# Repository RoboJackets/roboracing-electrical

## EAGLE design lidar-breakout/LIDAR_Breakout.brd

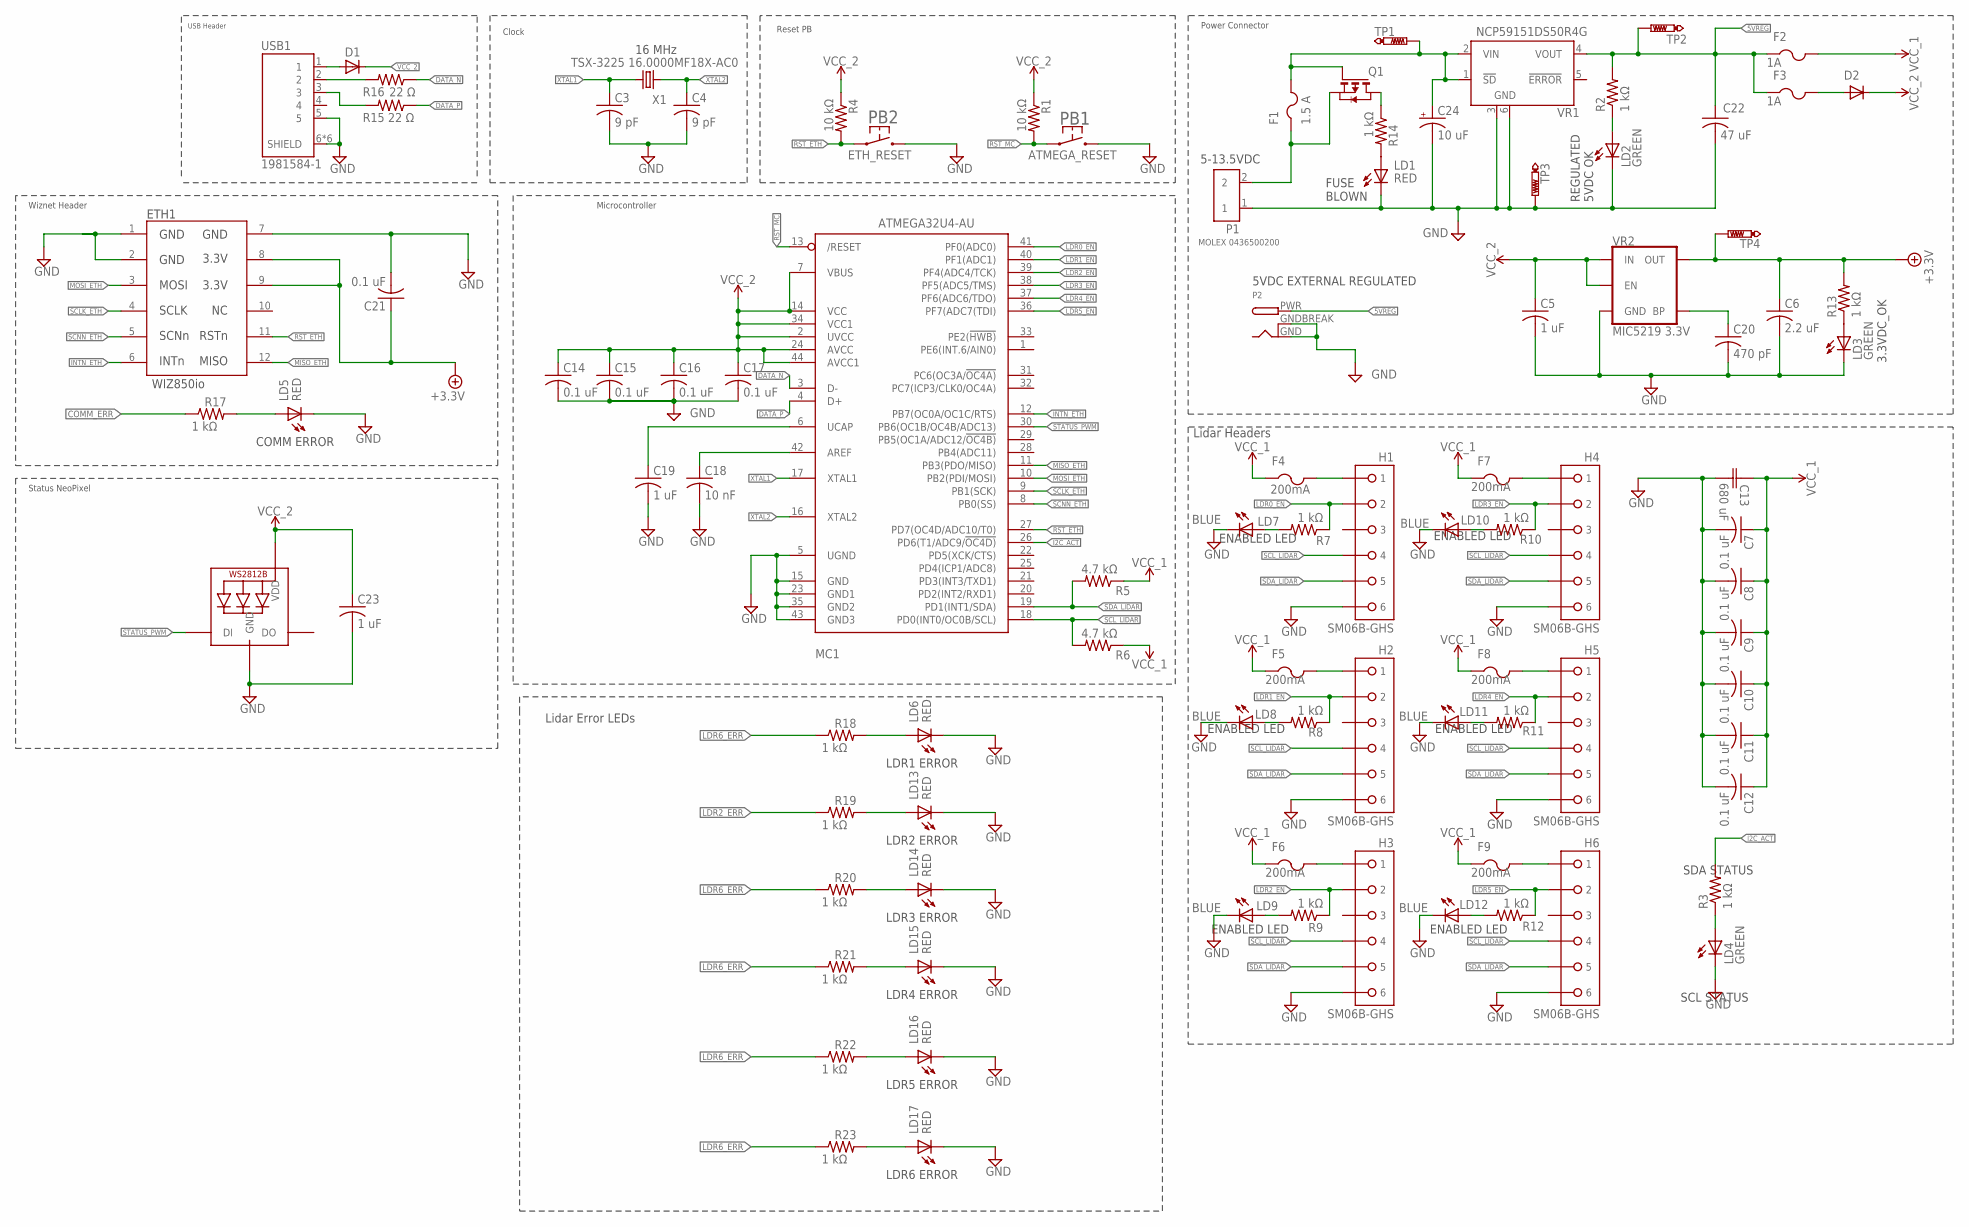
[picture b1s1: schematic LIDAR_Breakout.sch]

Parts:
C3, C4: 9 pF; C0603
C5, C19, C23: 1 uF; C0603
C6: 2.2 uF; C0603
C7, C8, C9, C10, C11, C12, C14, C15, C16, C17, C21: 0.1 uF; C0603
C13: 680 uF; CAP_PAN_EEE_D8
C18: 10 nF; C0603
C20: 470 pF; C0603
C22: 47 uF; C0805
C24: 10 uF; E2-5
D1, D2: DIODE-DO-214AC; DO-214AC
ETH1: WIZ850IO
F1: 1.5 A; 1812
F2, F3: 1A; R1206
F4, F5, F6, F7, F8, F9: 200mA; R1206
H1, H2, H3, H4, H5, H6: SM06B-GHS
LD1, LD5, LD6, LD13, LD14, LD15, LD16, LD17: RED; CHIP-LED0603
LD2, LD3, LD4: GREEN; CHIP-LED0603
LD7, LD8, LD9, LD10, LD11, LD12: BLUE; CHIP-LED0603
LED1: WS2812B5050; WS2812B
MC1: ATMEGA32U4-AU; TQFP44
P1: MOLEX 0436500200; MOLEX_0436500200
P2: DCBARRELPTH; DCJACK_2MM_PTH
PB1: ATMEGA_RESET; RESET_PB_RA
PB2: ETH_RESET; RESET_PB_RA
Q1: PMOS; SOT-23-3
R1, R4: 10 kΩ; R0603
R2, R3, R7, R8, R9, R10, R11, R12, R13, R14, R17, R18, R19, R20, R21, R22, R23: 1 kΩ; R0603
R5, R6: 4.7 kΩ; R0603
R15, R16: 22 Ω; R0603
TP1, TP2, TP4: PTR1B1,27; B1,27
TP3: PTR1PAD1-13; P1-13
USB1: 1981584-1; TE_1981584-1
VR1: NCP59151DS50R4G; TO263-5
VR2: MIC5219 3.3V; SOT23-5
X1: TSX-3225 16.0000MF18X-AC0; XTAL-3.2X2.5

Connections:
5VREG: C22.1, F2.1, F3.1, P2.PWR, R2.2, TP2.TP, VR1.4 (VOUT)
+3.3V: C6.1, C21.1, ETH1.8, ETH1.9, R13.2, TP4.TP, VR2.5 (OUT)
AREF: C18.1, MC1.42 (AREF)
COMM_ERR: R17.1
DATA_N: MC1.3 (D-), R16.1
DATA_P: MC1.4 (D+), R15.1
GND: C3.2, C4.2, C5.2, C6.2, C7.2, C8.2, C9.2, C10.2, C11.2, C12.2, C13.2 (22), C14.2, C15.2, C16.2, C17.2, C18.2, C19.2, C20.2, C21.2, C22.2, C23.2, C24.-, ETH1.1, ETH1.2, ETH1.7, H1.P$8 (6), H2.P$8 (6), H3.P$8 (6), H4.P$8 (6), H5.P$8 (6), H6.P$8 (6), LD1.C (K), LD2.C, LD3.C, LD4.C, LD5.C (K), LD6.C (K), LD7.C, LD8.C, LD9.C, LD10.C, LD11.C, LD12.C, LD13.C (K), LD14.C (K), LD15.C (K), LD16.C (K), LD17.C (K), LED1.3-GND (GND), MC1.5 (UGND), MC1.15 (GND), MC1.23 (GND1), MC1.35 (GND2), MC1.43 (GND3), P1.1, P2.GND, P2.GNDBREAK, PB1.P$3 (2), PB2.P$3 (2), TP3.TP, USB1.5, USB1.6 (SHIELD), USB1.7 (SHIELD), USB1.8 (SHIELD), USB1.9 (SHIELD), USB1.10 (SHIELD), USB1.11 (SHIELD), VR1.3 (GND), VR1.6 (GND), VR2.2 (GND)
I2C_ACT: MC1.26 (PD6(T1/ADC9/!OC4D)), R3.2
INTN_ETH: ETH1.6, MC1.12 (PB7(OC0A/OC1C/RTS))
LDR0_EN: H1.P$4 (2), MC1.41 (PF0(ADC0)), R7.1
LDR0_LED: LD7.A, R7.2
LDR1_EN: H2.P$4 (2), MC1.40 (PF1(ADC1)), R8.1
LDR1_LED: LD8.A, R8.2
LDR2_EN: H3.P$4 (2), MC1.39 (PF4(ADC4/TCK)), R9.1
LDR2_ERR: R19.1
LDR2_LED: LD9.A, R9.2
LDR3_EN: H4.P$4 (2), MC1.38 (PF5(ADC5/TMS)), R10.1
LDR3_LED: LD10.A, R10.2
LDR4_EN: H5.P$4 (2), MC1.37 (PF6(ADC6/TDO)), R11.1
LDR4_LED: LD11.A, R11.2
LDR5_EN: H6.P$4 (2), MC1.36 (PF7(ADC7(TDI)), R12.1
LDR5_LED: LD12.A, R12.2
LDR6_ERR: R18.1, R20.1, R21.1, R22.1, R23.1
MISO_ETH: ETH1.12, MC1.11 (PB3(PDO/MISO))
MOSI_ETH: ETH1.3, MC1.10 (PB2(PDI/MOSI))
unnamed: D1.A, USB1.1
unnamed: LD4.A, R3.1
unnamed: LD2.A, R2.1
unnamed: Q1.3 (D), R14.1
unnamed: LD3.A, R13.1
unnamed: LD1.A, R14.2
unnamed: D2.A, F3.2
unnamed: R16.2, USB1.2
unnamed: LD5.A, R17.2
unnamed: LD6.A, R18.2
unnamed: LD13.A, R19.2
unnamed: LD14.A, R20.2
unnamed: LD15.A, R21.2
unnamed: LD16.A, R22.2
unnamed: LD17.A, R23.2
unnamed: R15.2, USB1.3
unnamed: C20.1, VR2.4 (BP)
RST_ETH: ETH1.11, MC1.27 (PD7(OC4D/ADC10/T0)), PB2.P$1 (1), R4.2
RST_MC: MC1.13 (/RESET), PB1.P$1 (1), R1.2
SCLK_ETH: ETH1.4, MC1.9 (PB1(SCK))
SCL_LIDAR: H1.P$6 (4), H2.P$6 (4), H3.P$6 (4), H4.P$6 (4), H5.P$6 (4), H6.P$6 (4), MC1.18 (PD0(INT0/OC0B/SCL)), R6.2
SCNN_ETH: ETH1.5, MC1.8 (PB0(SS))
SDA_LIDAR: H1.P$7 (5), H2.P$7 (5), H3.P$7 (5), H4.P$7 (5), H5.P$7 (5), H6.P$7 (5), MC1.19 (PD1(INT1/SDA)), R5.2
STATUS_PWM: LED1.4-DIN (DI), MC1.30 (PB6(OC1B/OC4B/ADC13))
UCAP: C19.1, MC1.6 (UCAP)
UVCC: F1.1, P1.2, Q1.2 (S)
VCC_1: C7.1, C8.1, C9.1, C10.1, C11.1, C12.1, C13.1 (11), F2.2, F4.1, F5.1, F6.1, F7.1, F8.1, F9.1, R5.1, R6.1
VCC_2: C5.1, C14.1, C15.1, C16.1, C17.1, C23.1, D1.C, D2.C, LED1.1-VDD (VDD), MC1.2 (UVCC), MC1.7 (VBUS), MC1.14 (VCC), MC1.24 (AVCC), MC1.34 (VCC1), MC1.44 (AVCC1), R1.1, R4.1, VR2.1 (IN), VR2.3 (EN)
VCC_LDR0: F4.2, H1.P$3 (1)
VCC_LDR1: F5.2, H2.P$3 (1)
VCC_LDR2: F6.2, H3.P$3 (1)
VCC_LDR3: F7.2, H4.P$3 (1)
VCC_LDR4: F8.2, H5.P$3 (1)
VCC_LDR5: F9.2, H6.P$3 (1)
VIN: C24.+, F1.2, Q1.1 (G), TP1.TP, VR1.1 (!SD), VR1.2 (VIN)
XTAL1: C3.1, MC1.17 (XTAL1), X1.1
XTAL2: C4.1, MC1.16 (XTAL2), X1.3 (2)

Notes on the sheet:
Power Connector
Lidar Headers
Reset PB
Clock
Microcontroller
USB Header
Wiznet Header
5-13.5VDC
3.3VDC_OK
REGULATED 5VDC OK
FUSE BLOWN
SDA STATUS
SCL STATUS
ENABLED LED
Status NeoPixel
5VDC EXTERNAL REGULATED
16 MHz
COMM ERROR
LDR1 ERROR
LDR2 ERROR
LDR3 ERROR
LDR4 ERROR
LDR5 ERROR
LDR6 ERROR
Lidar Error LEDs

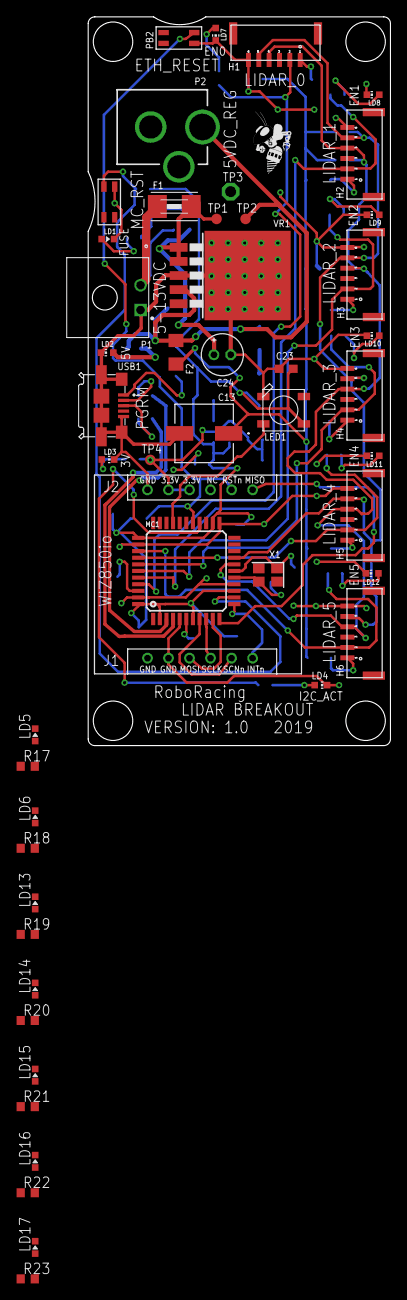
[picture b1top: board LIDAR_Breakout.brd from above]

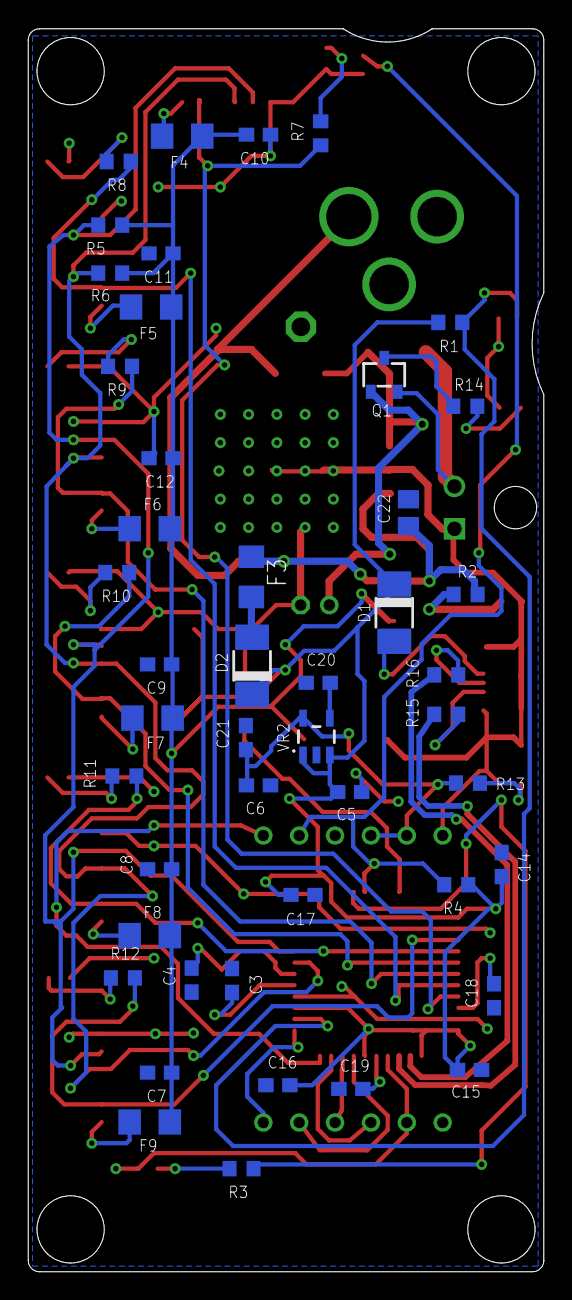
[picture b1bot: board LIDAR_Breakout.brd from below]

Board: 2 copper layers, 36.5 x 88.0 mm, 96 parts (46 on the bottom side), 60 nets.

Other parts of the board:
U$1: ROBOBUZZ0.4X; ROBOBUZZ_0.4X

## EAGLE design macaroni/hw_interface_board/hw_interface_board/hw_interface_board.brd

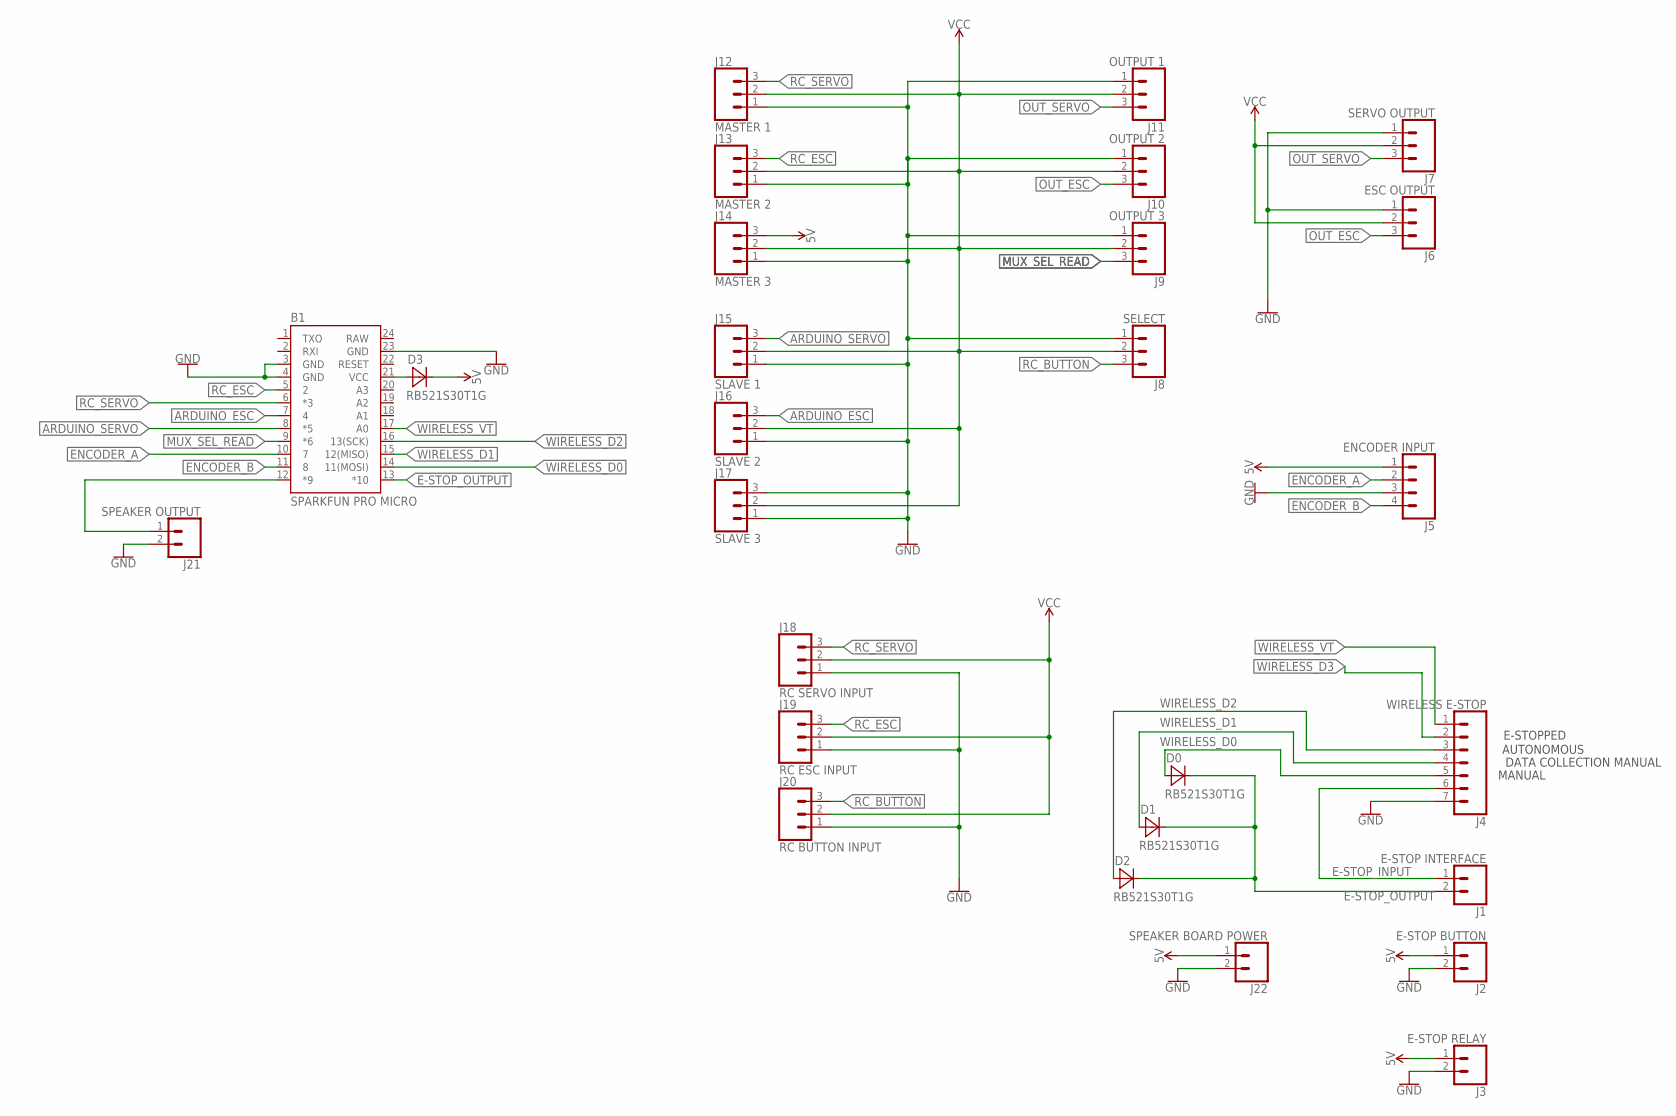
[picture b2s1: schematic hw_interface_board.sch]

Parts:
B1: SPARKFUN PRO MICRO; SPARKFUN_PRO_MICRO
D0, D1, D2, D3: RB521S30T1G; SOD523
J1: E-STOP INTERFACE; 1X02
J2: E-STOP BUTTON; 1X02
J3: E-STOP RELAY; 1X02
J4: WIRELESS E-STOP; 1X07
J5: ENCODER INPUT; 1X04
J6: ESC OUTPUT; 1X03
J7: SERVO OUTPUT; 1X03
J8: SELECT; 1X03
J9: OUTPUT 3; 1X03
J10: OUTPUT 2; 1X03
J11: OUTPUT 1; 1X03
J12: MASTER 1; 1X03
J13: MASTER 2; 1X03
J14: MASTER 3; 1X03
J15: SLAVE 1; 1X03
J16: SLAVE 2; 1X03
J17: SLAVE 3; 1X03
J18: RC SERVO INPUT; 1X03
J19: RC ESC INPUT; 1X03
J20: RC BUTTON INPUT; 1X03
J21: SPEAKER OUTPUT; 1X02
J22: SPEAKER BOARD POWER; 1X02

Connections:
5V: D3.C, J2.1, J3.1, J5.1, J14.3, J22.1
ARDUINO_ESC: B1.7 (4), J16.3
ARDUINO_SERVO: B1.8 (*5), J15.3
E-STOP_INPUT: J1.1, J4.6
E-STOP_OUTPUT: B1.13 (*10), D0.C, D1.C, D2.C, J1.2
ENCODER_A: B1.10 (7), J5.2
ENCODER_B: B1.11 (8), J5.4
GND: B1.3 (GND), B1.4 (GND), B1.23 (GND), J2.2, J3.2, J4.7, J5.3, J6.1, J7.1, J8.1, J9.1, J10.1, J11.1, J12.1, J13.1, J14.1, J15.1, J16.1, J17.1, J17.3, J18.1, J19.1, J20.1, J21.2, J22.2
MUX_SEL_READ: B1.9 (*6), J9.3
unnamed: B1.21 (VCC), D3.A
OUT_ESC: J6.3, J10.3
OUT_SERVO: J7.3, J11.3
RAW: B1.24 (RAW)
RC_BUTTON: J8.3, J20.3
RC_ESC: B1.5 (2), J13.3, J19.3
RC_SERVO: B1.6 (*3), J12.3, J18.3
SPEAKER_OUTPUT: B1.12 (*9), J21.1
VCC: J6.2, J7.2, J8.2, J9.2, J10.2, J11.2, J12.2, J13.2, J14.2, J15.2, J16.2, J17.2, J18.2, J19.2, J20.2
WIRELESS_D0: B1.14 (11(MOSI)), D0.A, J4.5
WIRELESS_D1: B1.15 (12(MISO)), D1.A, J4.4
WIRELESS_D2: B1.16 (13(SCK)), D2.A, J4.3
WIRELESS_D3: J4.2
WIRELESS_VT: B1.17 (A0), J4.1

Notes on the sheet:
E-STOPPED
AUTONOMOUS
DATA COLLECTION MANUAL
MANUAL

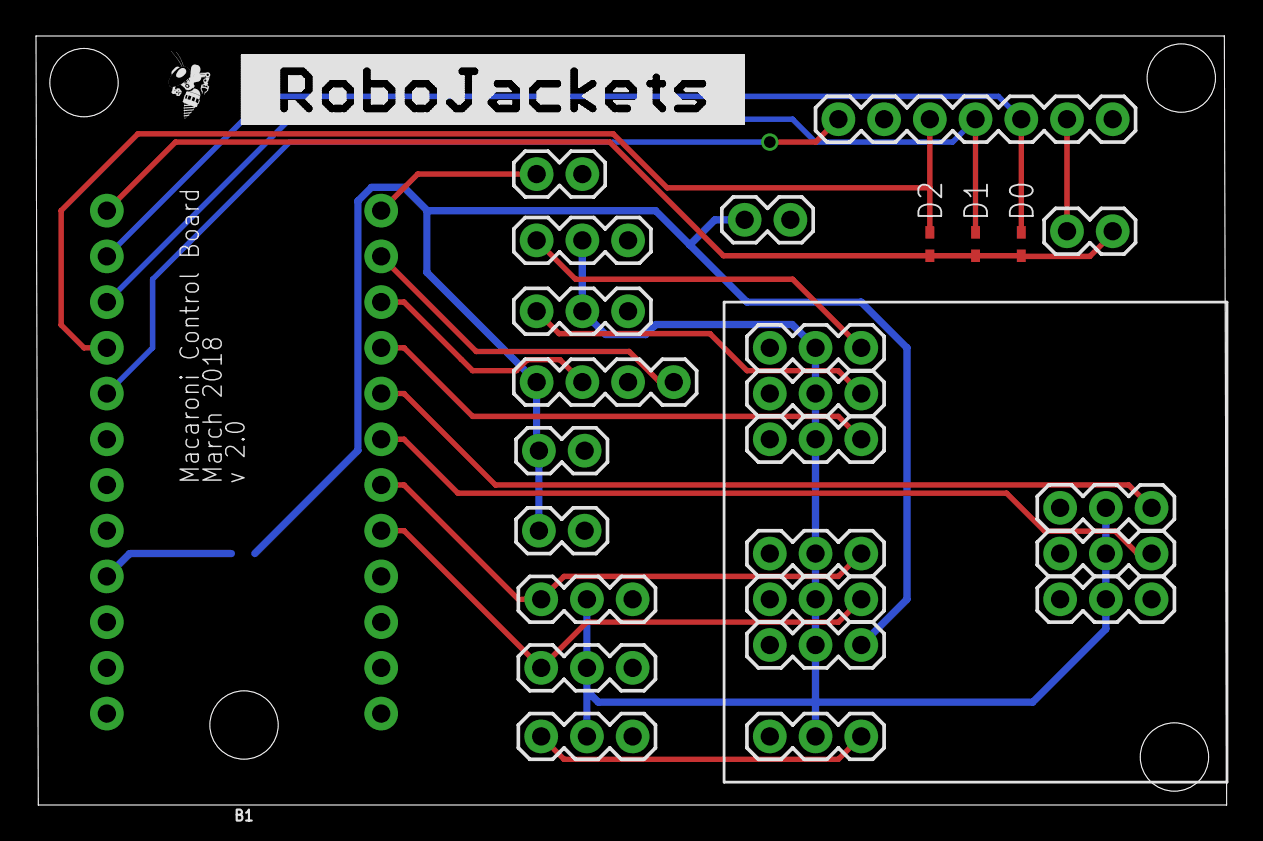
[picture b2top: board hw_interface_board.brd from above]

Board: 2 copper layers, 66.1 x 42.7 mm, 29 parts (1 on the bottom side), 21 nets.

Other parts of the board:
U$1: ROBOBUZZ_0.2X
U$2: ROBOJACKETS

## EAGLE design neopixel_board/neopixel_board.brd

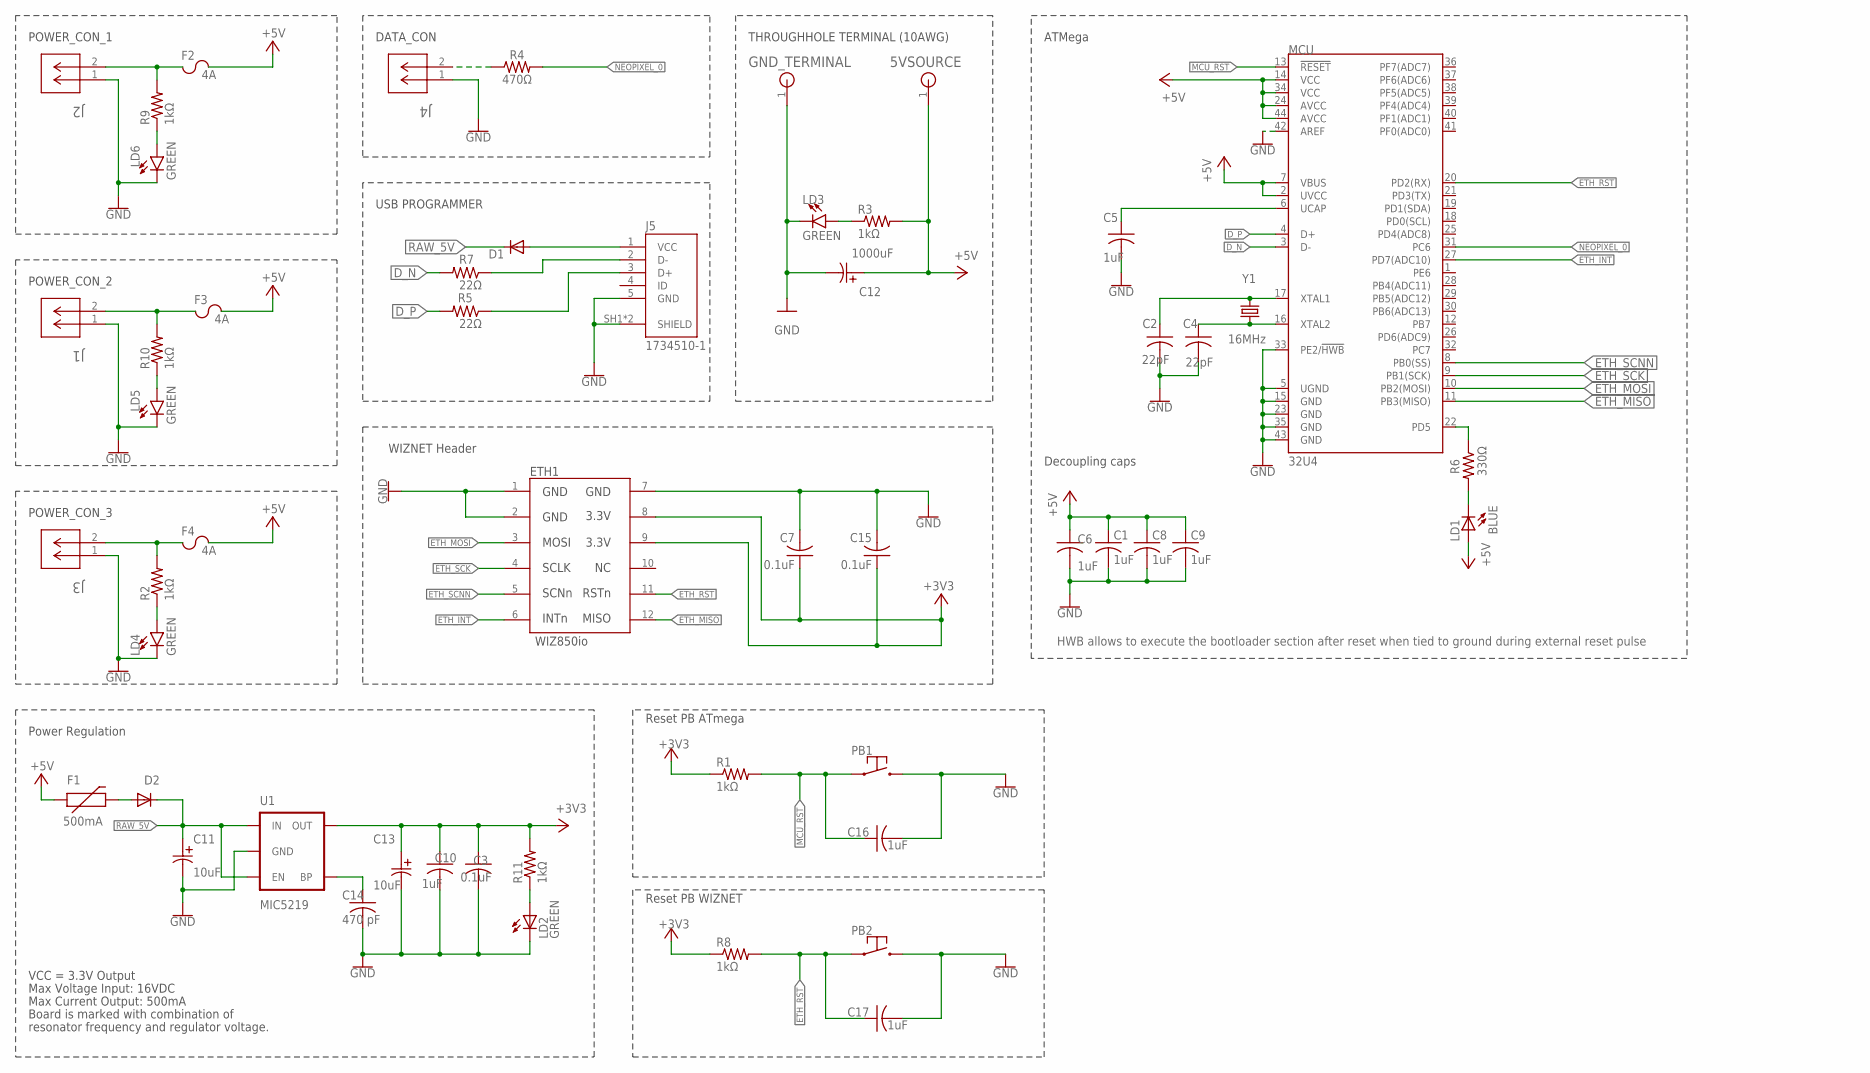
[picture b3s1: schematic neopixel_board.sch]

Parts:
5VSOURCE: THOLE_SOURCE
C1, C5, C6, C8, C9, C10, C16, C17: 1uF; C0603
C2, C4: 22pF; C0603
C3, C7, C15: 0.1uF; C0603
C11, C13: 10uF; CAP_4_X_5.4
C12: 1000uF; PCAP_8X112
C14: 470 pF; C0603
D1, D2: DIODESOD; SOD-323
ETH1: WIZ850IO
F1: 500mA; PTC-1206
F2, F3, F4: 4A; 3557-2
GND_TERMINAL: THOLE_SOURCE
J1, J2, J3, J4: SSW-102-02-T-S-RA; CON2_1X2_TR_SSQ
J5: 1734510-1; TE_1734510-1
LD1: BLUE; LED-0603
LD2, LD3, LD4, LD5, LD6: GREEN; LED-0603
MCU: 32U4; TQFP44
PB1, PB2: PTS645PTS645_SMD1; PTS645_SMD
R1, R8: 1kΩ; R0603
R2, R3, R9, R10, R11: 1kΩ; 0603-RES
R4: 470Ω; 0603
R5, R7: 22Ω; 0603-RES
R6: 330Ω; 0603-RES
U1: MIC5219; SOT23-5
Y1: 16MHz; CRYSTAL-SMD-5X3

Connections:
+3V3: C3.1, C7.1, C10.1, C13.1 (11), C15.1, ETH1.8, ETH1.9, R1.1, R8.1, R11.2, U1.5 (OUT)
+5V: 5VSOURCE.1, C1.1, C6.1, C8.1, C9.1, C12.1 (11), F1.1, F2.3 (2), F2.4 (2), F3.3 (2), F3.4 (2), F4.3 (2), F4.4 (2), LD1.A, MCU.2 (UVCC), MCU.7 (VBUS), MCU.14 (VCC), MCU.24 (AVCC), MCU.34 (VCC), MCU.44 (AVCC), R3.2
D_N: MCU.3 (D-), R7.2
D_P: MCU.4 (D+), R5.2
ETH_INT: ETH1.6, MCU.27 (PD7(ADC10))
ETH_MISO: ETH1.12, MCU.11 (PB3(MISO))
ETH_MOSI: ETH1.3, MCU.10 (PB2(MOSI))
ETH_RST: C17.1, ETH1.11, MCU.20 (PD2(RX)), PB2.P$1 (1), PB2.P$2 (1), R8.2
ETH_SCK: ETH1.4, MCU.9 (PB1(SCK))
ETH_SCNN: ETH1.5, MCU.8 (PB0(SS))
GND: C1.2, C2.2, C3.2, C4.2, C5.2, C6.2, C7.2, C8.2, C9.2, C10.2, C11.2 (22), C12.2 (22), C13.2 (22), C14.2, C15.2, C16.2, C17.2, ETH1.1, ETH1.2, ETH1.7, GND_TERMINAL.1, J1.1, J2.1, J3.1, J4.1, J5.5 (GND), J5.SH1 (SHIELD), J5.SH2 (SHIELD), LD2.C, LD3.C, LD4.C, LD5.C, LD6.C, MCU.5 (UGND), MCU.15 (GND), MCU.23 (GND), MCU.33 (PE2/!HWB), MCU.35 (GND), MCU.42 (AREF), MCU.43 (GND), PB1.P$3 (2), PB1.P$4 (2), PB2.P$3 (2), PB2.P$4 (2), U1.2 (GND)
MCU_RST: C16.1, MCU.13 (!RESET), PB1.P$1 (1), PB1.P$2 (1), R1.2
unnamed: C4.1, MCU.16 (XTAL2), Y1.1
unnamed: C2.1, MCU.17 (XTAL1), Y1.3 (2)
unnamed: J5.2 (D-), R7.1
unnamed: C5.1, MCU.6 (UCAP)
unnamed: C14.1, U1.4 (BP)
unnamed: J5.3 (D+), R5.1
unnamed: LD1.C, R6.2
unnamed: D1.2 (A), J5.1 (VCC)
unnamed: D2.2 (A), F1.2
unnamed: F2.1, F2.2 (1), J2.2, R9.2
unnamed: F3.1, F3.2 (1), J1.2, R10.2
unnamed: F4.1, F4.2 (1), J3.2, R2.2
unnamed: J4.2, R4.1
unnamed: LD4.A, R2.1
unnamed: LD5.A, R10.1
unnamed: LD6.A, R9.1
unnamed: LD3.A, R3.1
unnamed: LD2.A, R11.1
NEOPIXEL_0: MCU.31 (PC6), R4.2
RAW_5V: C11.1 (11), D1.1 (C), D2.1 (C), U1.1 (IN), U1.3 (EN)
TXLED: MCU.22 (PD5), R6.1

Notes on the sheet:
Max Voltage Input: 16VDC
Max Current Output: 500mA
Board is marked with combination of
resonator frequency and regulator voltage.
VCC = 3.3V Output
Reset PB ATmega
WIZNET Header
USB PROGRAMMER
Power Regulation
ATMega
THROUGHHOLE TERMINAL (10AWG)
Reset PB WIZNET
POWER_CON_1
POWER_CON_2
POWER_CON_3
DATA_CON
Decoupling caps
HWB allows to execute the bootloader section after reset when tied to ground during external reset pulse

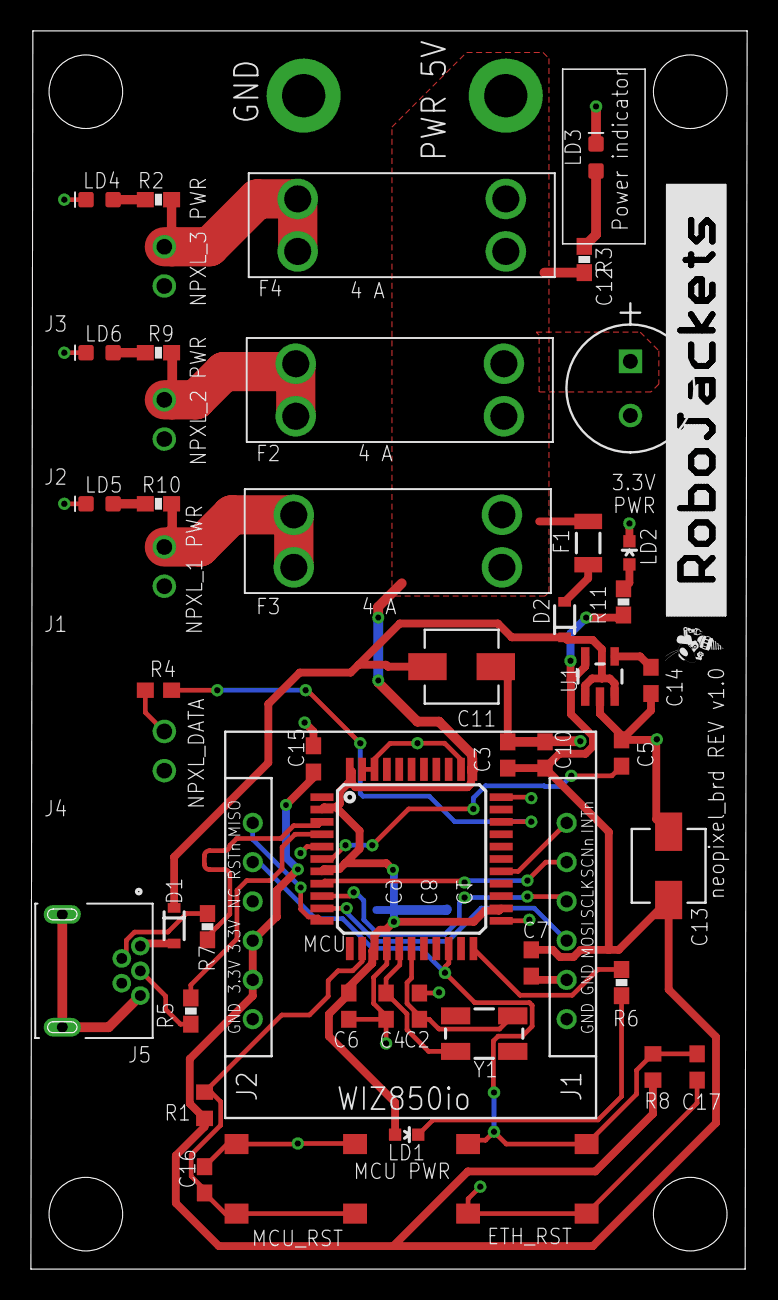
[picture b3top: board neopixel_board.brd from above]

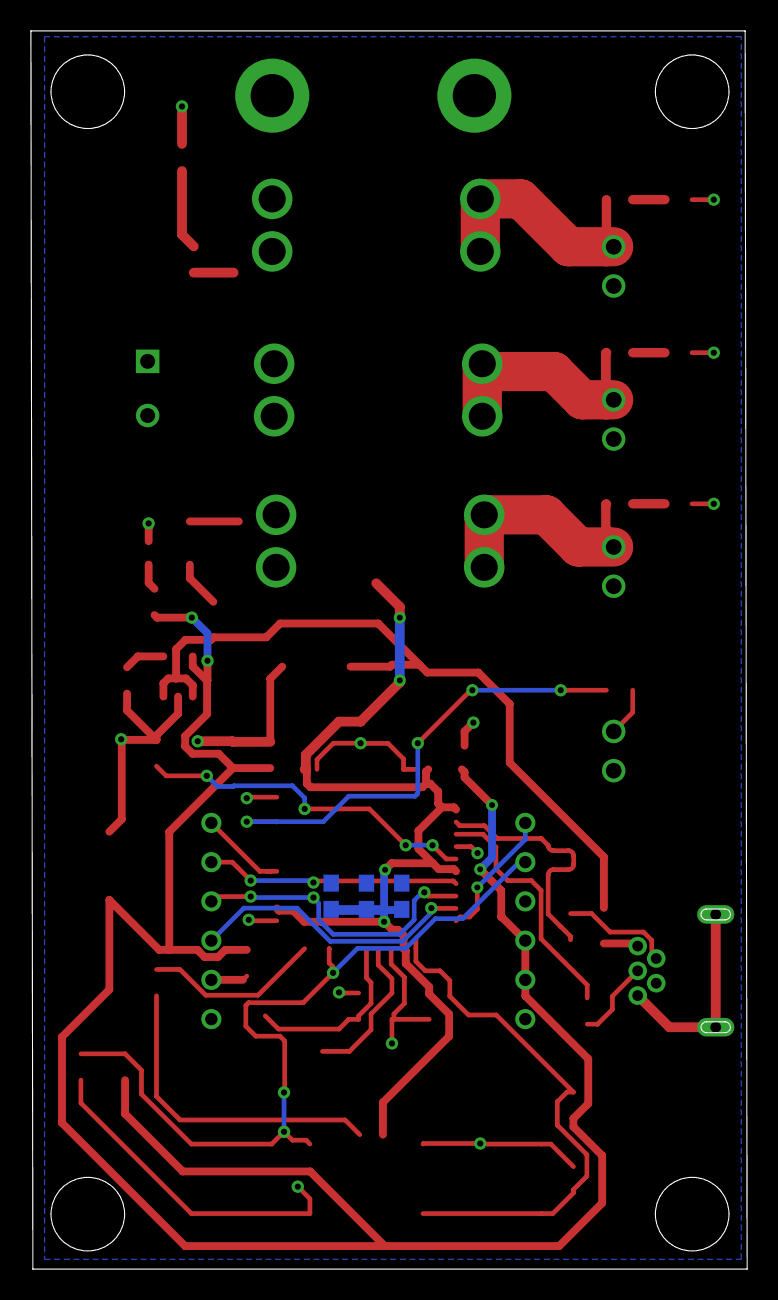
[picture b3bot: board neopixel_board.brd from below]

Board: 2 copper layers, 46.4 x 80.1 mm, 55 parts (3 on the bottom side), 33 nets.

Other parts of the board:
U$1: ROBOJACKETS
U$2: ROBOBUZZ_0.2X

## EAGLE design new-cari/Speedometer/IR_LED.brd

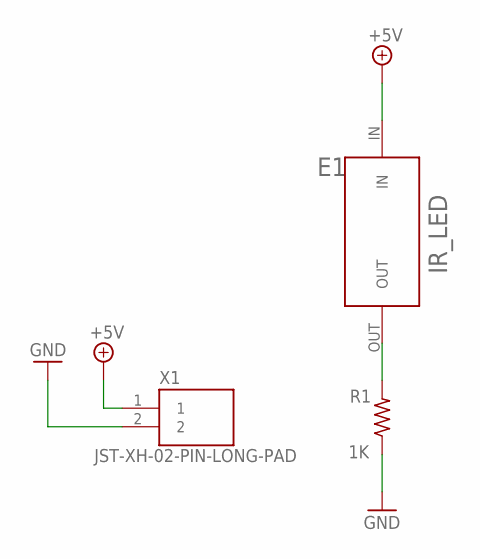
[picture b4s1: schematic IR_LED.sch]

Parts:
E1: IR_LED; STD_FP
R1: 1K; R0603
X1: JST-XH-02-PIN-LONG-PAD; JST-XH-02-PACKAGE-LONG-PAD

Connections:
+5V: E1.IN, X1.1
GND: R1.1, X1.2
unnamed: E1.OUT, R1.2

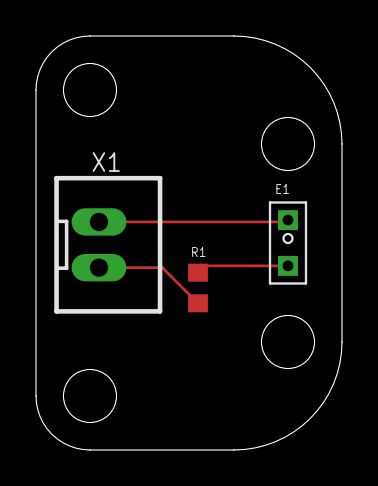
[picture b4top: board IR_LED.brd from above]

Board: 2 copper layers, 17.0 x 23.0 mm, 3 parts (0 on the bottom side), 3 nets.

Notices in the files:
parts and their libraries:
SparkFun-IC-Power: Licensing: Creative Commons ShareAlike 4.0 International - https://creativecommons.org/licenses/by-sa/4.0
